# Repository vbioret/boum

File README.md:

# boum !!!

> This is a toy created to teach code and electronic basics to my young sons

## Finished toy

## Second prototype

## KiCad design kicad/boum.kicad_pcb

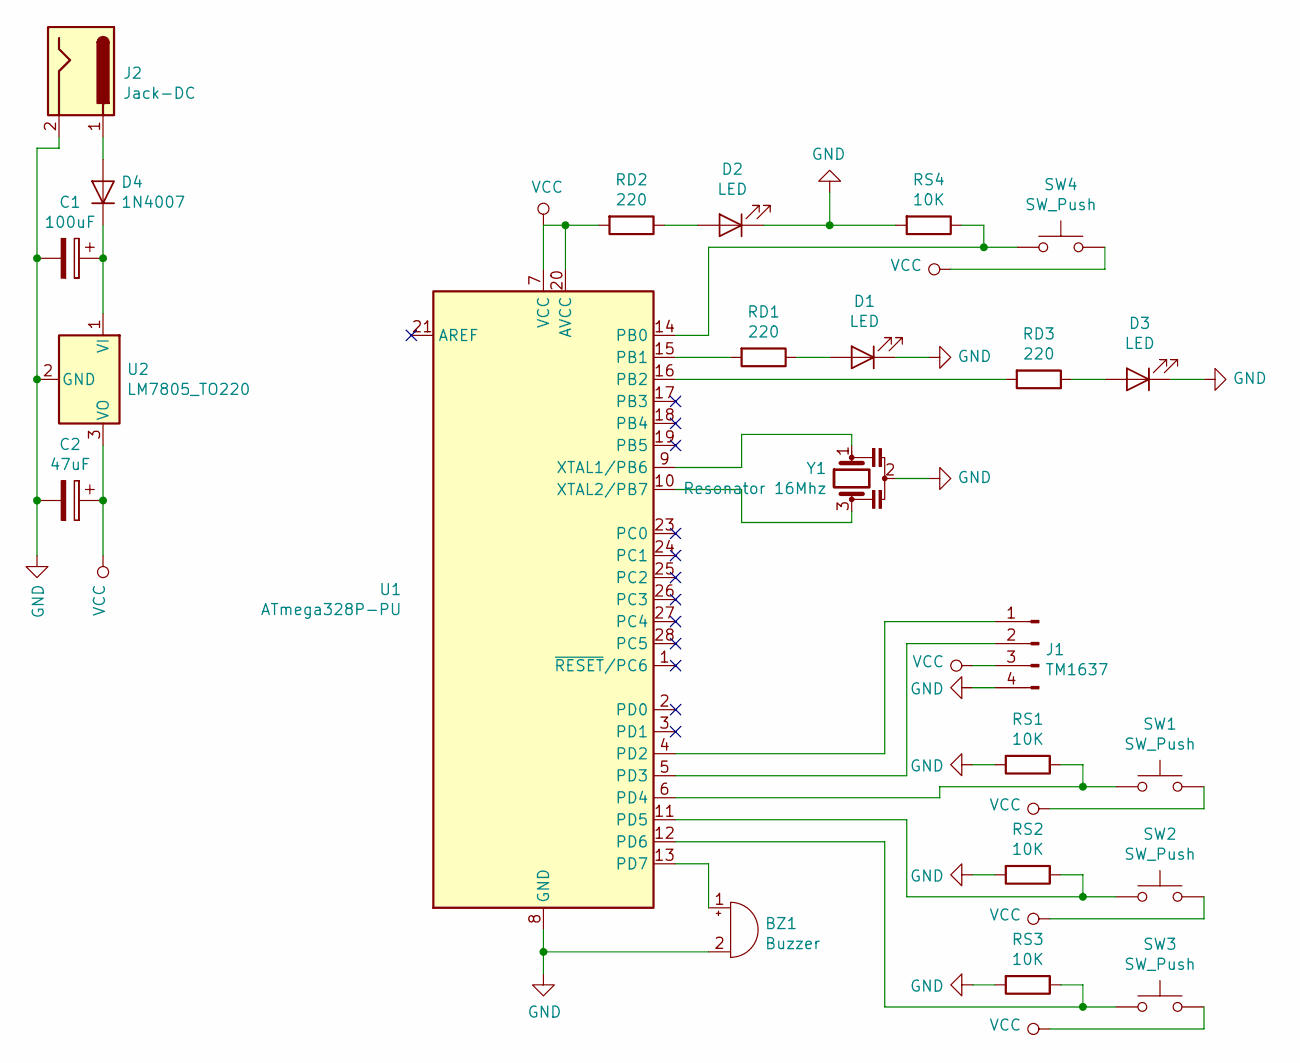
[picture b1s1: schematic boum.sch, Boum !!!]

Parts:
BZ1: Buzzer; Buzzer_12x9.5RM7.6
C1: 100uF; CP_Radial_D4.0mm_P2.00mm
C2: 47uF; CP_Radial_D5.0mm_P2.50mm
D1, D2, D3: LED; LED_D5.0mm
D4: 1N4007; D_DO-41_SOD81_P10.16mm_Horizontal
J1: TM1637; PinHeader_1x04_P2.54mm_Vertical
J2: Jack-DC; BarrelJack_Horizontal
RD1, RD2, RD3: 220; R_Axial_DIN0207_L6.3mm_D2.5mm_P10.16mm_Horizontal
RS1, RS2, RS3, RS4: 10K; R_Axial_DIN0207_L6.3mm_D2.5mm_P10.16mm_Horizontal
SW1, SW2, SW3, SW4: SW_Push; PinHeader_1x02_P2.54mm_Vertical
U1: ATmega328P-PU; DIP-28_W7.62mm
U2: LM7805_TO220; TO-220-3_Vertical
Y1: Resonator 16Mhz; Resonator-3Pin_W6.0mm_H3.0mm

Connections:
GND: BZ1.2 (+), C1.2, C2.2, D1.1 (K), D2.1 (K), D3.1 (K), J1.4, J2.2, RS1.2, RS2.2, RS3.2, RS4.2, U1.8 (GND), U1.22 (GND), U2.2 (GND), Y1.2
unnamed: BZ1.1 (-), U1.13 (PD7)
unnamed: C1.1, D4.1 (K), U2.1 (VI)
unnamed: D1.2 (A), RD1.1
unnamed: D2.2 (A), RD2.1
unnamed: D3.2 (A), RD3.1
unnamed: D4.2 (A), J2.1
unnamed: J1.1, U1.4 (PD2)
unnamed: J1.2, U1.5 (PD3)
unnamed: RD1.2, U1.15 (PB1)
unnamed: RD3.2, U1.16 (PB2)
unnamed: RS1.1, SW1.1, U1.6 (PD4)
unnamed: RS2.1, SW2.1, U1.11 (PD5)
unnamed: RS3.1, SW3.1, U1.12 (PD6)
unnamed: RS4.1, SW4.1, U1.14 (PB0)
unnamed: U1.9 (XTAL1/PB6), Y1.1
unnamed: U1.10 (XTAL2/PB7), Y1.3
VCC: C2.1, J1.3, RD2.2, SW1.2, SW2.2, SW3.2, SW4.2, U1.7 (VCC), U1.20 (AVCC), U2.3 (VO)

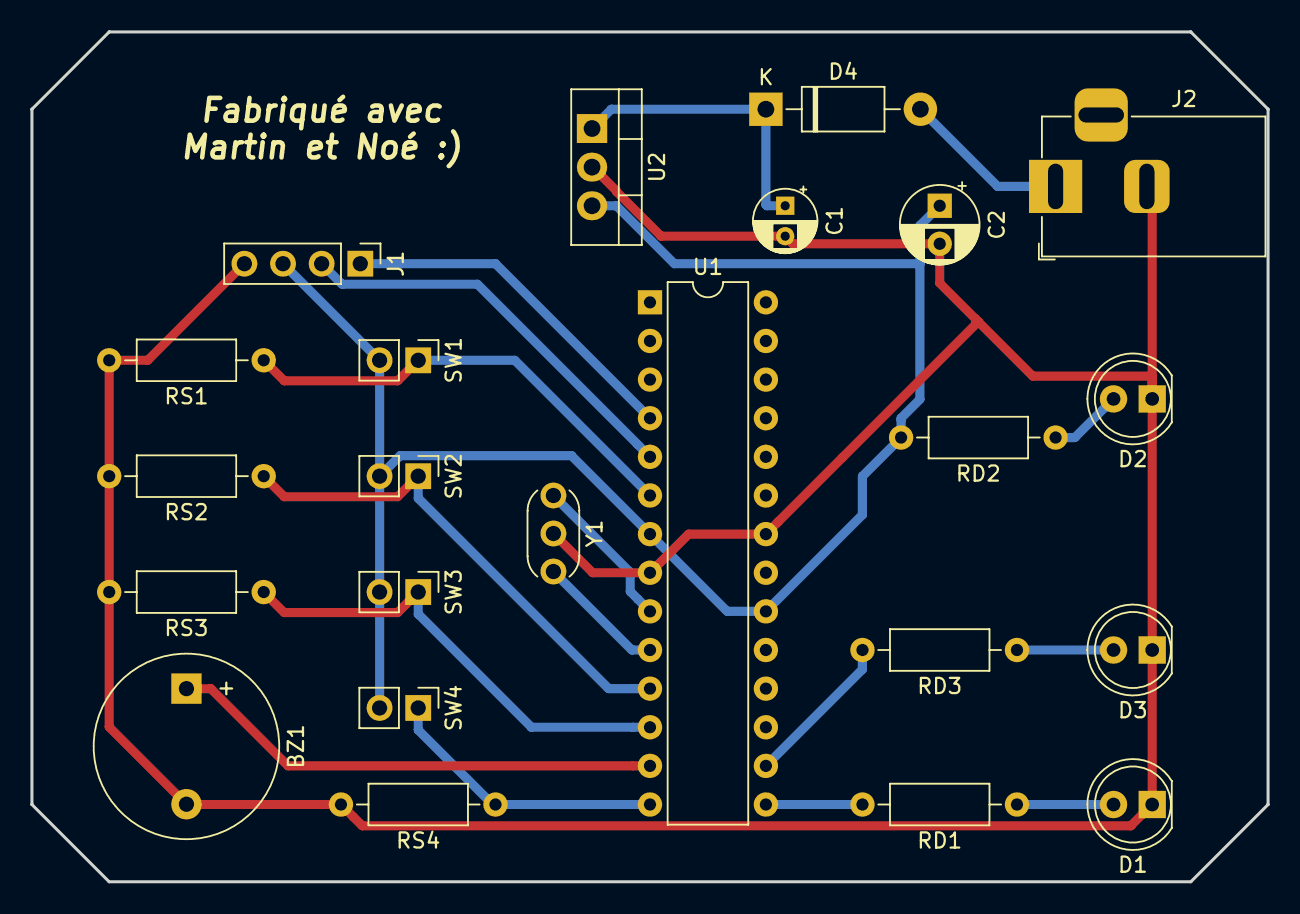
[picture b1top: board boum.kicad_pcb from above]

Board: 2 copper layers, 81.3 x 55.9 mm, 23 parts (0 on the bottom side), 18 nets.

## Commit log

2019-02-21 Arduino code
2019-02-21 Kicad schemas and PCB
2019-02-21 Images
2019-02-21 README.md
2019-02-21 Create LICENSE
